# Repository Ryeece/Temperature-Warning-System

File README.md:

# Temperature-Warning-System

Embedded temperature monitoring and warning system using an Arduino Mega 2560, DHT11, 16×2 LCD, and custom KiCad shield PCB

## Overview

Using the Arduino Mega I measured the temperature with a DHT11 sensor and had the live temperature reading displayed on the 16×2 LCD. When the set temperature threshold was exceeded a warning LED turns on with a warning message on the 16×2 LCD. For sensor faults the warning LED turns on with a check sensor message on the 16×2 LCD. Finally a custom Mega shield PCB was designed in KiCad.

## Features

- Live temperature measurement
- Temperature threshold warning
- Sensor fault detection
- LCD status messages
- Standalone battery operation
- Custom PCB shield

## Hardware Used

- ELEGOO Arduino Mega 2560
- DHT11 temperature and humidity module
- 1602A V2.0 16×2 LCD
- 10 kΩ potentiometer
- LED
- 220 Ω resistor
- Breadboard
- Jumper wires
- Battery power supply
- Custom Arduino Mega shield PCB designed in KiCad to replace the breadboard and jumper wires

## System Operation

First the DHT11 takes the temperature reading, then it sends the data to the Mega and the Mega processes the reading using the uploaded code and displays the temperature on the LCD. If the temperature threshold is exceeded the warning LED turns on and a warning message is displayed on the LCD. Finally the function `isnan()` is used to detect an invalid sensor reading which activates the warning LED and error message on the LCD.

## Breadboard Prototype
The system was first built and tested on a breadboard before being transferred into the custom Arduino Mega shield PCB design.

The temperature threshold was temporarily set to 29.8°C so the high-temperature warning could be tested at room temperature.

- Normal operation — LCD shows live temperature and Normal temp, LED off:

- High-temperature warning — LCD shows TEMP TOO HIGH, warning LED on:

- Sensor fault — LCD shows the sensor error message, warning LED on:

## Testing and Fault Handling

The system was initially tested on a breadboard to verify the temperature monitoring, warning LED, LCD messages and sensor fault detection before transferring the circuit to the custom PCB.

The manufactured PCB was then assembled and connected to the Arduino Mega 2560 to verify that the completed hardware operated correctly.

| Test | Expected Result | Result |
|------|-----------------|--------|
| Temperature below threshold | LED off and normal-temperature message displayed on the LCD | Pass |
| Temperature above threshold | LED on and high-temperature warning message displayed on the LCD | Pass |
| DHT11 signal disconnected | Warning LED on and sensor error message displayed on the LCD | Pass |
| Battery-powered operation | System operates without a laptop connection | Pass |
| Assembled PCB functionality | All components operate correctly through the custom PCB | Pass |

### Sensor Fault Detection

To test the `isnan()` fault handling, I deliberately disconnected the DHT11 signal. The Arduino detected the invalid sensor reading, activated the warning LED and displayed an error message on the LCD.

### Physical PCB Testing

After soldering the components and headers onto the manufactured PCB, the shield was connected to the Arduino Mega 2560.

The system operated successfully during its initial testing, with the LCD displaying live temperature readings and the warning LED responding to the programmed conditions.

The normal-temperature, high-temperature warning and sensor fault states were successfully tested using the assembled PCB.

The completed system was also tested using a standalone 9V battery connected to the Arduino's power input, confirming that it could operate without a computer connection.

No changes to the PCB design were required for the system to function. However, a possible intermittent solder connection was identified as an area for further inspection.

## PCB Design

The PCB was designed as an Arduino Mega shield so it could plug directly into the Mega.

- A 16-pin header was added for the 16×2 LCD and a 3-pin header for the DHT11
- The LED, 220 Ω resistor and 10 kΩ potentiometer were placed on the shield
- The breadboard prototype was used to help plan the PCB layout
- ERC and DRC were used to check the design
- The final layout was checked in KiCad's 3D Viewer

KiCad schematic:

KiCad PCB layout:

3D view of the PCB Mega shield:

The Mega-template header footprints mainly establish the correct physical positions. In place of the female headers, male headers will be soldered underneath the physical PCB to allow connection to the Mega 2560, and female headers will be soldered on top for removable connections for the DHT11 and LCD.

## PCB Manufacturing and Assembly

After completing the PCB design in KiCad, I generated the Gerber and drill files required for manufacturing. These files were uploaded to JLCPCB, where I ordered the custom two-layer PCB.

Once the manufactured boards arrived, I assembled the circuit by soldering the components and pin headers onto the PCB using the soldering facilities at university.

The completed PCB was then connected to the Arduino Mega 2560 and powered using a 9V battery through the Arduino's barrel jack.

During initial testing, I encountered a minor connectivity issue, potentially caused by a solder joint. However, the PCB operated successfully without requiring any modifications to the original design.

This was my first experience taking a PCB design through the complete process of manufacturing, physical assembly and functional testing.

**1. Manufactured PCB before assembly**

**2. Assembled PCB**

**3. PCB underside and solder joints**

**4. Completed and operational system**

## Problems Encountered and Fixes

| Problem | Cause | Fix |
|---|---|---|
| External LED did not light | Both LED legs were connected to the same breadboard node | Repositioned the LED so each leg was connected to a different node |
| LCD displayed dark blocks instead of text | D7 was connected incorrectly | Corrected the LCD wiring so D7 connected to the correct LCD pin |
| Invalid DHT11 reading | Sensor communication failed when the signal was disconnected | Added `isnan()` fault detection, an LCD error message and warning LED activation |
| KiCad ERC/DRC warnings | Unused and duplicated connections in the Arduino Mega template | Used No Connect flags, `PWR_FLAG`s and intentional exclusions where appropriate |

## Final Result

The temperature warning system has been successfully developed, manufactured, assembled and tested.

After completing the circuit design and programming, I designed a custom Arduino Mega shield PCB using KiCad. The PCB was manufactured by JLCPCB, and I soldered all the components myself using the facilities at university.

Following assembly, the system operated successfully without requiring any PCB design modifications. A minor connectivity issue was encountered, potentially caused by a solder joint, but the system was able to function correctly.

The completed system successfully:

- Measures and displays live temperature readings on a 16×2 LCD.

- Detects temperatures exceeding the programmed threshold and displays a high-temperature warning.

- Detects sensor faults and displays an error message.

- Operates independently using a 9V battery connected to the Arduino Mega.

This project allowed me to develop practical skills in electronic circuit design, microcontroller programming, PCB design, soldering, troubleshooting and hardware testing. It was particularly rewarding to see a PCB I had independently designed operate successfully after manufacturing and assembly.

## Project Files

- [Arduino Code](code/Temperature%20Warning%20System.ino)
- [KiCad PCB Files](pcb/)
- [PCB Manufacturing Files (Gerber ZIP)](pcb/Temperature-Warning-System-Gerber-Files.zip.zip)
- [Project Report](documentation/Temperature%20Warning%20system%20report.pdf)

## Future Improvements

A temperature-controlled fan could be added, using PWM (Pulse Width Modulation) to automatically adjust the fan speed based on the measured temperature. This would allow the system to actively regulate temperature rather than simply provide a warning.

User-adjustable buttons could be implemented to allow the temperature warning threshold to be changed without modifying and uploading the Arduino code.

The power supply could be improved by replacing the 9V battery with a more efficient rechargeable power source, allowing the system to operate independently for longer periods.

A protective enclosure could also be designed to house the Arduino, custom PCB and other components, making the completed system more compact and suitable for practical use.
Eventually, the Arduino Mega can be replaced with a microcontroller mounted directly on the PCB.

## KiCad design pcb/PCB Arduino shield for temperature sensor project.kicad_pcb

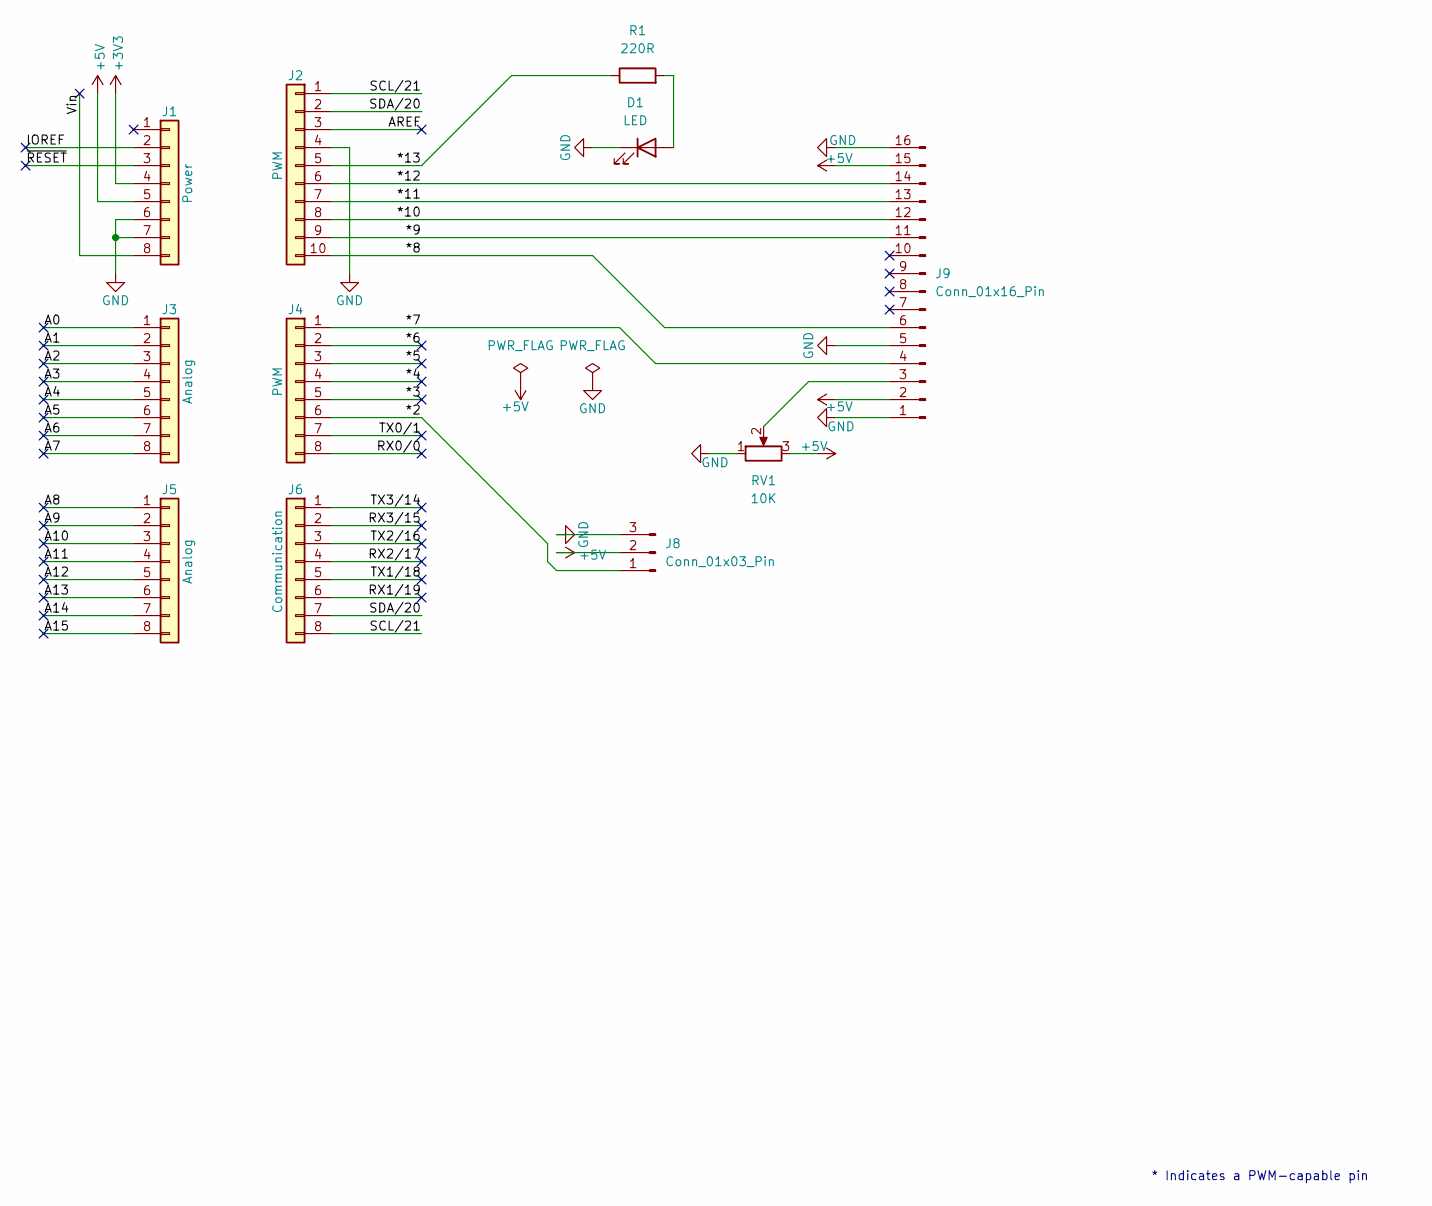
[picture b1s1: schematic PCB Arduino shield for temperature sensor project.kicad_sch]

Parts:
D1: LED; LED_D5.0mm
J1: Power; PinSocket_1x08_P2.54mm_Vertical
J2: PWM; PinSocket_1x10_P2.54mm_Vertical
J3, J5: Analog; PinSocket_1x08_P2.54mm_Vertical
J4: PWM; PinSocket_1x08_P2.54mm_Vertical
J6: Communication; PinSocket_1x08_P2.54mm_Vertical
J8: Conn_01x03_Pin; PinHeader_1x03_P2.54mm_Vertical
J9: Conn_01x16_Pin; PinHeader_1x16_P2.54mm_Vertical
R1: 220R; R_Axial_DIN0207_L6.3mm_D2.5mm_P10.16mm_Horizontal
RV1: 10K; Potentiometer_ACP_CA9-V10_Vertical

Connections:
+3V3: J1.4
+5V: J1.5, J8.2, J9.2, J9.15, RV1.3
/*2: J4.6, J8.1
/*3: J4.5
/*4: J4.4
/*5: J4.3
/*6: J4.2
/*7: J4.1, J9.4
/*8: J2.10, J9.6
/*9: J2.9, J9.11
/*10: J2.8, J9.12
/*11: J2.7, J9.13
/*12: J2.6, J9.14
/*13: J2.5, R1.1
/A0: J3.1
/A1: J3.2
/A2: J3.3
/A3: J3.4
/A4: J3.5
/A5: J3.6
/A6: J3.7
/A7: J3.8
/A8: J5.1
/A9: J5.2
/A10: J5.3
/A11: J5.4
/A12: J5.5
/A13: J5.6
/A14: J5.7
/A15: J5.8
/AREF: J2.3
/IOREF: J1.2
/RX0/0: J4.8
/RX1/19: J6.6
/RX2/17: J6.4
/RX3/15: J6.2
/SCL/21: J2.1, J6.8
/SDA/20: J2.2, J6.7
/TX0/1: J4.7
/TX1/18: J6.5
/TX2/16: J6.3
/TX3/14: J6.1
/Vin: J1.8
/~RESET: J1.3
GND: D1.1 (K), J1.6, J1.7, J2.4, J8.3, J9.1, J9.5, J9.16, RV1.1
unnamed: D1.2 (A), R1.2
unnamed: J9.3, RV1.2

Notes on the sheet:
* Indicates a PWM-capable pin

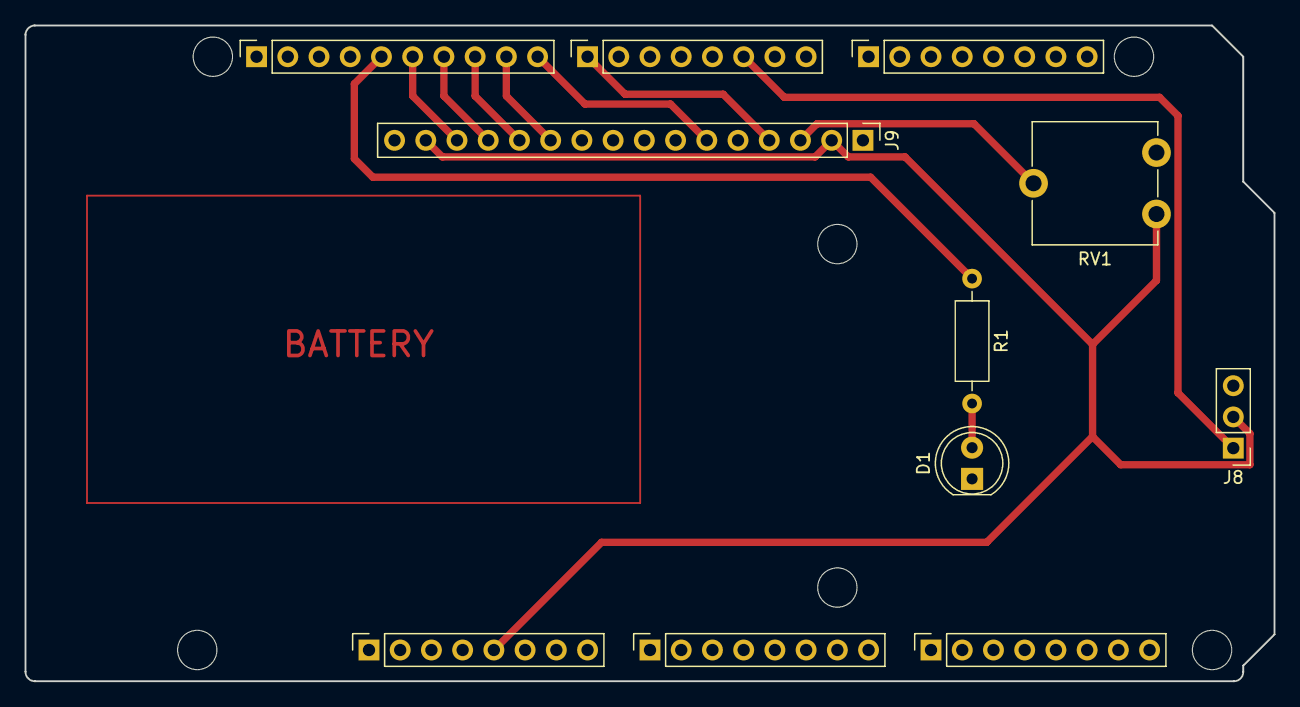
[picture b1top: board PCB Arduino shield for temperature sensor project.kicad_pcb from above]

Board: 2 copper layers, 101.6 x 53.3 mm, 17 parts (0 on the bottom side), 14 nets.

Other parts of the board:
MH1, MH2, MH3, MH4, MH5, MH6: MountingHole_3.2mm
